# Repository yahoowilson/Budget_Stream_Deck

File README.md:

# Logan's Budget Stream Deck
This is the first custom project that I made entirely myself with blueprint. I wanted a stream deck but did not want to pay $150, so I thought it would be cool to try and make my own. So here is my attempt at a "budget" stream deck with 8 switches, a rotary encoder and an oled screen. all programmable. The BOM is viewable below or downloadable in excel or pdf format to access the links.

Bill of Materials (also in .xlsx or .pdf format above)

I found cheaper keycaps on adafruit instead of mechanicalkeyboards.com

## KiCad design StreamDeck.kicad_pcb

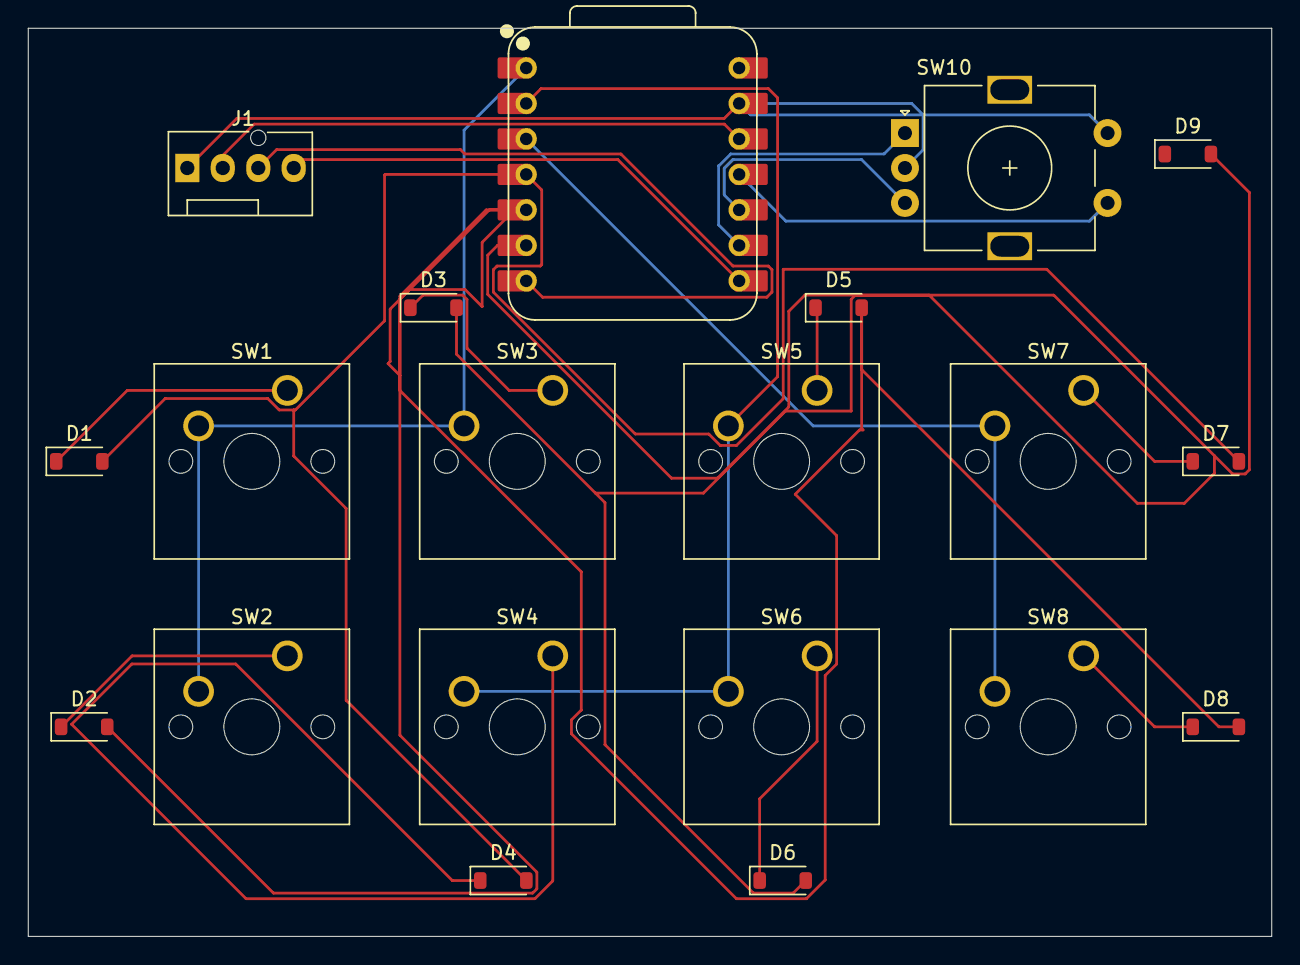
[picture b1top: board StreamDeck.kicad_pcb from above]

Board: 2 copper layers, 89.0 x 65.0 mm, 20 parts (0 on the bottom side), 21 nets.

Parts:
D1, D2, D3, D4, D5, D6, D7, D8, D9: D_Small; D_SOD-123
J1: Conn_01x04; FanPinHeader_1x04_P2.54mm_Vertical
SW1, SW2, SW3, SW4, SW5, SW6, SW7, SW8: SW_Push; SW_Cherry_MX_1.00u_PCB
SW10: RotaryEncoder_Switch; RotaryEncoder_Alps_EC11E-Switch_Vertical_H20mm
U1: XIAO-ESP32-C3-DIP; XIAO-ESP32C3-DIP

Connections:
+3.3V: J1.2, U1.12 (VCC_3V3)
/COL0: D1.2 (A), D4.2 (A), D7.2 (A), U1.4 (GPIO5/A3/D3)
/COL1: D2.2 (A), D5.2 (A), D8.2 (A), U1.5 (GPIO6/D4/SDA)
/COL2: D3.2 (A), D6.2 (A), D9.2 (A), U1.6 (GPIO7/D5/SCL)
/ENC_A: SW10.A, U1.9 (GPIO8/D8/SCK)
/ENC_B: SW10.B, U1.10 (GPIO9/D9/MISO)
/ENC_SW: SW10.S1, U1.11 (GPIO10/D10/MOSI)
/ROW0: SW1.2, SW2.2, SW3.2, U1.1 (GPIO2/A0/D0)
/ROW1: SW4.2, SW5.2, SW6.2, U1.2 (GPIO3/A1/D1)
/ROW2: SW7.2, SW8.2, U1.3 (GPIO4/A2/D2)
/SCL: J1.3, U1.7 (GPIO21/D6/TX)
/SDA: J1.4, U1.8 (GPIO20/D7/RX)
GND: J1.1, SW10.C, SW10.S2, U1.13 (GND)
unnamed: D1.1 (K), SW1.1
unnamed: D2.1 (K), SW2.1
unnamed: D3.1 (K), SW3.1
unnamed: D4.1 (K), SW4.1
unnamed: D5.1 (K), SW5.1
unnamed: D6.1 (K), SW6.1
unnamed: D7.1 (K), SW7.1
unnamed: D8.1 (K), SW8.1

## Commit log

2025-12-11 added more to readme
    Expanded project description to include details about the design and its context.
2025-12-11 Reworded README
2025-12-12 organized
2025-12-14 added firmware
2025-12-14 added gerber zip
2025-12-17 added revised files
